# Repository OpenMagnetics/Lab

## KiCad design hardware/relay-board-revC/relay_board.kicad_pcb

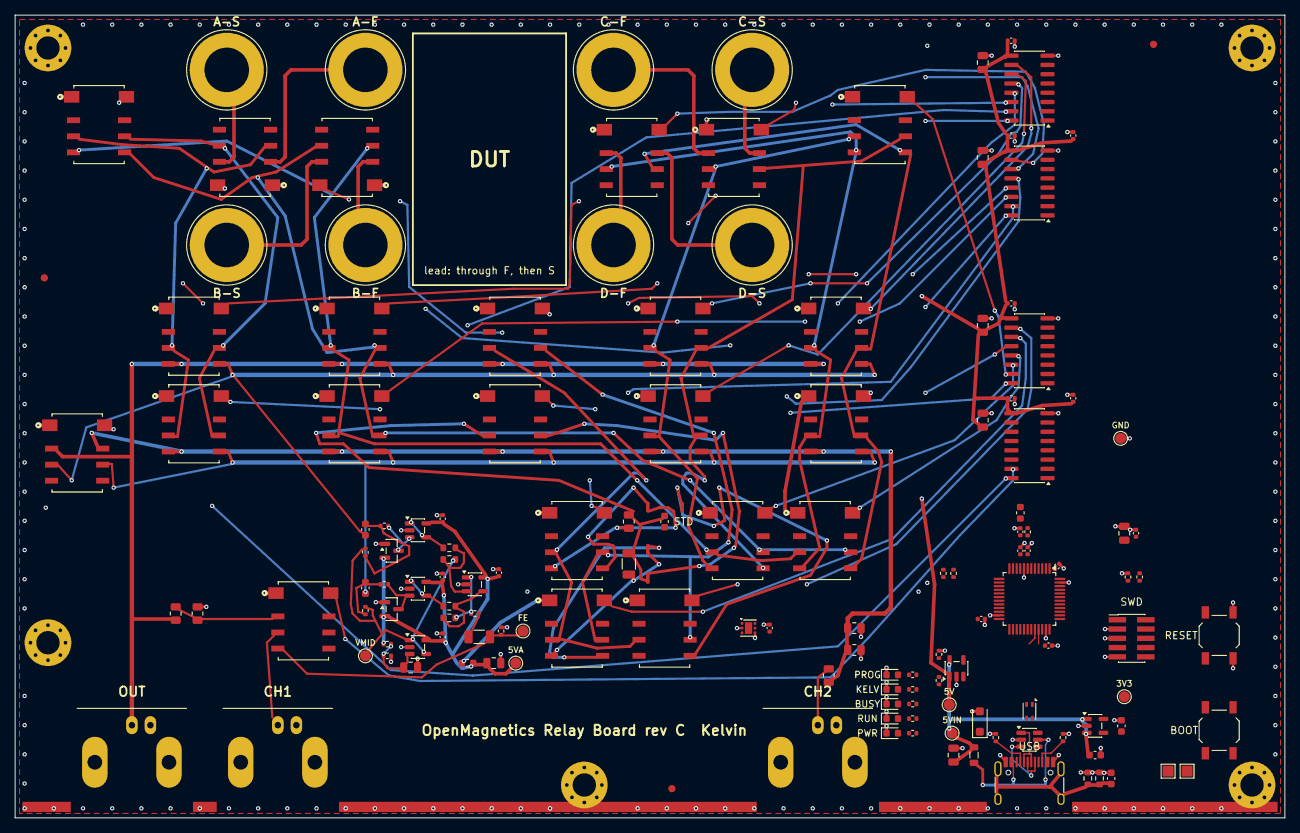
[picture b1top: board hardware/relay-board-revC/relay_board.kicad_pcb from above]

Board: 4 copper layers, 174.0 x 110.0 mm, 157 parts (0 on the bottom side), 126 nets.

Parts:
BOND1, BOND2, BOND3, BOND4, BOND5: GND bonding strip; GND_BondingStrip
C1, C2, C23, C29, C32, C33, C34, C35: C_0805_2012Metric
C3, C4, C20, C21, C30, C31: C_0603_1608Metric
C5, C6, C7, C8, C9, C10, C11, C12, C15, C16, C17, C18, C19, C25, C26, C27, C28, C36: C_0402_1005Metric
C22: C_1206_3216Metric
D1, D5, D6, D7, D8: LED_0603_1608Metric
D2: SOT-23-6
D3, D4: SOT-23
D9: D_SOD-123F
FB1: L_0805_2012Metric
FB2, FB3: L_0603_1608Metric
FID1, FID2, FID3: Fiducial_1mm_Mask2mm
H1, H2, H3, H4, H5: MountingHole_3.2mm_M3_Pad_Via
J1: USB_C_Receptacle_HRO_TYPE-C-31-M-12
J6, J7, J9: BNC_Amphenol_B6252HB-NPP3G-50_Horizontal
J8: PinHeader_2x05_P1.27mm_Vertical_SMD
J10, J11, J12, J13, J14, J15, J16, J17: Banana_Jack_1Pin
K1, K2, K3, K4, K5, K6, K7, K8, K9, K10, K11, K12, K13, K14, K15, K16, K17, K18, K19, K20, K21, K22, K23: G6K-2F-RF-S; Relay_Omron_G6K-2F-RF-S
L1: L_CommonModeChoke_Coilank_ACM2012
NT1, NT2, NT4, NT5: NetTie-2_SMD_Pad0.5mm
R1, R2, R3, R4, R10, R17, R20, R21, R22, R23, R28, R29, R30, R31, R32, R33, R34, R35, R38, R39, R40, R41: R_0402_1005Metric
R5, R12, R13, R14, R15, R16: R_0805_2012Metric
R18: R_1206_3216Metric
R24, R25, R26, R27, R36, R37: R_0603_1608Metric
SW1, SW2: SW_SPST_TL3342
TP1, TP2: TestPoint_Pad_1.5x1.5mm
TP3, TP4, TP5, TP6, TP7, TP8, TP9: TestPoint_Pad_D1.5mm
U1: LQFP-48_7x7mm_P0.5mm
U2, U3, U4, U6: SOIC-16_3.9x9.9mm_P1.27mm
U5, U7, U8, U9, U10, U11: SOT-23-5
U12: WSON-6-1EP_2x2mm_P0.65mm_EP1x1.6mm

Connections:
/+3V3: C2.1, C4.1, C8.1, C9.1, C16.1, C17.1, C36.1, FB3.1, J8.1, R3.1, R32.1, R38.2, R39.2, R41.2, SW1.1, TP2.1, TP5.1, U1.1, U1.24, U1.36, U1.48, U5.5, U12.5
/+3V3A: C18.1, C19.1, FB3.2, U1.9
/+5V: C5.1, C6.1, C7.1, C10.1, C11.1, C12.1, C32.1, C33.1, C34.1, C35.1, FB2.1, K1.1, K2.1, K3.1, K4.1, K5.1, K6.1, K7.1, K8.1, K9.1, K10.1, K11.1, K12.1, K13.1, K14.1, K15.1, K16.1, K17.1, K18.1, K19.1, K20.1, K21.1, K22.1, K23.1, TP3.1, U2.9, U3.9, U4.9, U6.9, U11.1
/+5VA: C25.1, C26.1, C27.1, C28.1, C29.1, D3.2, D4.2, FB2.2, R30.1, TP6.1, U7.5, U8.5, U9.5, U10.5
/+5V_IN: C1.1, C3.1, FB1.2, TP4.1, U5.1, U5.3, U11.5
/BOOT0: R4.1, R17.2, TP1.1, U1.44
/BOOT_SW: R17.1, SW1.2
/BUSY_A: D6.2, R33.2
/CAL_E: K9.3, K19.3, K20.3, K21.3
/CAL_ES: K9.6, K19.6, K20.6, K21.6
/CAL_F: C30.2, K10.3, NT2.1, R5.2, R18.2
/CAL_FS: K10.6, NT2.2
/CC1: J1.A5, R1.1
/CC2: J1.B5, R2.1
/CH1_BNC: J7.1, K23.3
/CH1_NODE: K23.2, R12.2, R13.1
/CH2_NODE: J9.1, R16.2
/COIL_EN: R40.1, U1.25, U11.4
/COIL_FLT: R41.1, U1.26, U11.3
/DUTS_A: J11.1, K11.7
/DUTS_B: J13.1, K12.7
/DUTS_C: J15.1, K13.7
/DUTS_D: J17.1, K14.7
/DUT_A: J10.1, K11.2
/DUT_B: J12.1, K12.2
/DUT_C: J14.1, K13.2
/DUT_D: J16.1, K14.2
/FE_AMP: R25.2, R28.1, U9.1
/FE_BN: R24.1, U8.1, U8.4
/FE_BP: R26.1, U7.1, U7.4
/FE_DM: R24.2, R25.1, U9.4
/FE_DP: R26.2, R27.1, U9.3
/FE_INN: C21.2, R22.1, R23.1
/FE_INP: C20.2, R20.1, R21.1
/FE_N: D4.3, R23.2, U8.3
/FE_OUT: C22.2, K23.4, R29.1, TP8.1
/FE_P: D3.3, R21.2, U7.3
/FE_R: C22.1, R28.2
/GND: BOND1.1, BOND2.1, BOND3.1, BOND4.1, BOND5.1, C1.2, C2.2, C3.2, C4.2, C5.2, C6.2, C7.2, C8.2, C9.2, C10.2, C11.2, C12.2, C15.2, C16.2, C17.2, C18.2, C19.2, C23.2, C25.2, C26.2, C27.2, C28.2, C29.2, C31.2, C32.2, C33.2, C34.2, C35.2, C36.2, D1.1, D2.2, D3.1, D4.1, D5.1, D6.1, D7.1, D8.1, D9.2, H1.1, H2.1, H3.1, H4.1, H5.1, J1.A1, J1.A12, J1.B1, J1.B12, J6.2, J7.2, J8.3, J8.5, J8.9, J9.2, R1.2, R2.2, R4.2, R13.2, R14.2, R15.2, R29.2, R31.2, R36.2, R37.2, R40.2, SW2.2, TP9.1, U1.8, U1.23, U1.35, U1.47, U2.8, U3.8, U4.8, U5.2, U6.8, U7.2, U8.2, U9.2, U10.2, U11.2, U12.2, U12.4
/GPIO1: U1.14, U2.1
/GPIO2: U1.15, U2.2
/GPIO3: U1.16, U2.3
/GPIO4: U1.17, U2.4
/GPIO5: U1.18, U2.5
/GPIO6: U1.19, U2.6
/GPIO7: U1.20, U2.7
/GPIO8: U1.43, U3.1
/GPIO9: U1.42, U3.2
/GPIO10: U1.41, U3.3
/GPIO11: U1.40, U3.4
/GPIO12: U1.39, U3.5
/GPIO13: U1.38, U3.6
/GPIO14: U1.13, U3.7
/GPIO15: U1.10, U4.1
/GPIO16: U1.6, U4.2
/GPIO17: U1.5, U4.3
/GPIO18: U1.4, U4.4
/GPIO19: U1.3, U4.5
/GPIO20: U1.46, U4.6
/GPIO21: U1.45, U4.7
/GPIO22: U1.12, U6.1
/GPIO23: U1.11, U6.2
/I2C_SCL: R38.1, U1.21, U12.1
/I2C_SDA: R39.1, U1.22, U12.6
/K1_COIL: K1.8, U2.16
/K2_COIL: K2.8, U2.15
/K3_COIL: K3.8, U2.14
/K4_COIL: K4.8, U2.13
/K5_COIL: K5.8, U2.12
/K6_COIL: K6.8, U2.11
/K7_COIL: K7.8, U2.10
/K8_COIL: K8.8, U3.16
/K9_COIL: K9.8, U3.15
/K10_COIL: K10.8, U3.14
/K11_COIL: K11.8, U3.13
/K12_COIL: K12.8, U3.12
/K13_COIL: K13.8, U3.11
/K14_COIL: K14.8, U3.10
/K15_COIL: K15.8, U4.16
/K16_COIL: K16.8, U4.15
/K17_COIL: K17.8, U4.14
/K18_COIL: K18.8, U4.13
/K19_COIL: K19.8, U4.12
/K20_COIL: K20.8, U4.11
/K21_COIL: K21.8, U4.10
/K22_COIL: K22.8, U6.16
/K23_COIL: K23.8, U6.15
/KELVIN_A: D7.2, R34.2
/LED_BUSY: R33.1, U1.29
/LED_KELVIN: R34.1, U1.28
/LED_PROG: R35.1, U1.27
/LED_RUN: R10.1, U1.30
/NRST: C15.1, J8.10, R3.2, SW2.1, U1.7
/PROG_A: D8.2, R35.2
/PWR_A: D5.2, R32.2
/RAIL_HI: J6.1, K1.4, K3.4, K5.4, K7.4, K9.4, K22.2, R12.1
/RAIL_LO: K2.4, K4.4, K6.4, K8.4, K10.4, K22.7, R14.1, R15.1, R16.1
/RUN_A: D1.2, R10.2
/SA: K1.6, K2.6, K11.6, K15.6
/SB: K3.6, K4.6, K12.6, K15.5, K17.6, K18.6
/SC: K5.6, K6.6, K13.6, K16.6, K17.5
/SD: K7.6, K8.6, K14.6, K16.5, K18.5
/SNS_HI: C20.1, K1.5, K3.5, K5.5, K7.5, K9.5, K22.3
/SNS_LO: C21.1, K2.5, K4.5, K6.5, K8.5, K10.5, K22.6
/STD1_F: K19.4, NT1.1, R5.1
/STD1_S: K19.5, NT1.2
/STD2_F: K20.4, NT4.1, R18.1
/STD2_S: K20.5, NT4.2
/STD3_F: C30.1, K21.4, NT5.1
/STD3_S: K21.5, NT5.2
/SWCLK: J8.4, U1.37
/SWDIO: J8.2, U1.34
/TA: K1.3, K2.3, K11.3, K15.3
/TB: K3.3, K4.3, K12.3, K15.4, K17.3, K18.3
/TC: K5.3, K6.3, K13.3, K16.3, K17.4
/TD: K7.3, K8.3, K14.3, K16.4, K18.4
/USB_DM: L1.2, U1.32
/USB_DM_CON: D2.1, J1.A7, J1.B7
/USB_DM_ESD: D2.6, L1.3
/USB_DP: L1.1, U1.33
/USB_DP_CON: D2.3, J1.A6, J1.B6
/USB_DP_ESD: D2.4, L1.4
/USB_SHIELD: C31.1, J1.SH, R36.1, R37.1
/VBUS: D2.5, D9.1, FB1.1, J1.A4, J1.A9, J1.B4, J1.B9
/VMID: R20.2, R22.2, R27.2, TP7.1, U10.1, U10.4
/VMID_DIV: C23.1, R30.2, R31.1, U10.3

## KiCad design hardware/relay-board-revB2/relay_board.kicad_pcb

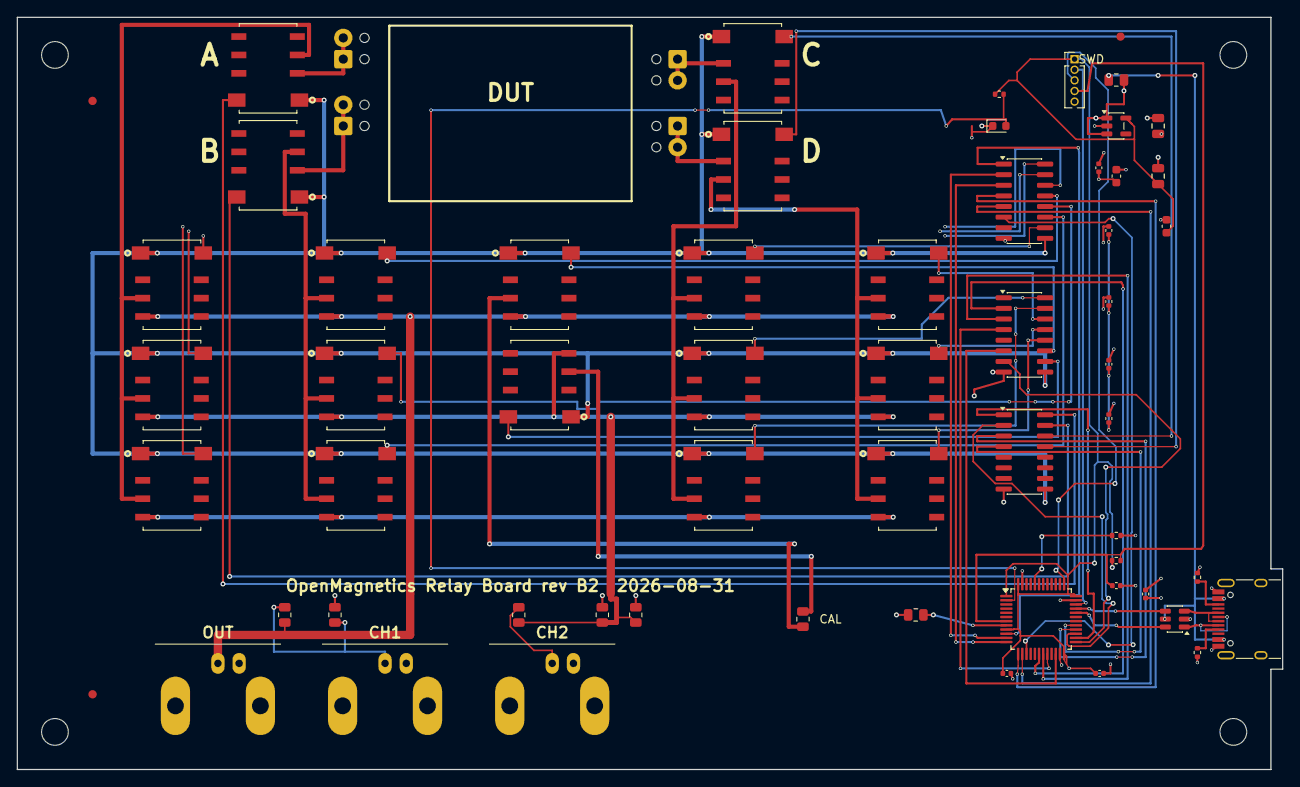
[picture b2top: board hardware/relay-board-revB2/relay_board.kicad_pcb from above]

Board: 4 copper layers, 151.4 x 90.0 mm, 67 parts (0 on the bottom side), 67 nets.

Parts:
C1, C2: C_0805_2012Metric
C3, C4: C_0603_1608Metric
C5, C6, C7, C8, C9, C10, C11, C12, C15: C_0402_1005Metric
D1: LED_0603_1608Metric
D2: SOT-23-6
FID1, FID2, FID3: Fiducial_1mm_Mask2mm
H1, H2, H3, H4: MountingHole_3.2mm_M3
J1: USB_C_Receptacle_HRO_TYPE-C-31-M-12
J2, J3, J4, J5: TerminalBlock_Phoenix_MPT-0,5-2-2.54_1x02_P2.54mm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; TerminalBlock_Phoenix_MPT-0,5-2-2.54_1x02_P2.54mm_Horizontal
J6, J7, J9: BNC_Amphenol_B6252HB-NPP3G-50_Horizontal
J8: PinHeader_1x05_P1.27mm_Vertical
K1, K2, K3, K4, K5, K6, K7, K8, K9, K10, K11, K12, K13, K14, K15, K16, K17, K18: G6K-2F-RF-S; Relay_Omron_G6K-2F-RF-S
R1, R2, R3, R4, R10: R_0402_1005Metric
R5, R9, R11, R12, R13, R14, R15, R16: R_0805_2012Metric
U1: LQFP-48_7x7mm_P0.5mm
U2, U3, U4: SOIC-16_3.9x9.9mm_P1.27mm
U5: SOT-23-5

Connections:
/+3V3: C2.1, C4.1, C8.1, C9.1, J8.1, R3.1, R10.1, U1.1, U1.9, U1.24, U1.36, U1.48, U5.5
/+5V: C1.1, C3.1, C5.1, C6.1, C7.1, C10.1, C11.1, C12.1, K1.1, K2.1, K3.1, K4.1, K5.1, K6.1, K7.1, K8.1, K9.1, K10.1, K11.1, K12.1, K13.1, K14.1, K15.1, K16.1, K17.1, K18.1, R9.2, U2.9, U3.9, U4.9, U5.1, U5.3
/AGND: J6.2, J7.2, J9.2, R11.1, R13.2, R14.2, R15.2
/BOOT0: R4.1, U1.44
/CAL_E: K13.3, R5.1
/CAL_F: K14.3, R5.2
/CC1: J1.A5, R1.1
/CC2: J1.B5, R2.1
/CH1_NODE: J7.1, R12.2, R13.1
/CH2_NODE: J9.1, R16.2
/DUT_A: J2.1, J2.2, K15.2
/DUT_B: J3.1, J3.2, K16.2
/DUT_C: J4.1, J4.2, K17.2
/DUT_D: J5.1, J5.2, K18.2
/GND: C1.2, C2.2, C3.2, C4.2, C5.2, C6.2, C7.2, C8.2, C9.2, C10.2, C11.2, C12.2, C15.2, D1.1, D2.2, J1.A1, J1.A12, J1.B1, J1.B12, J1.S1, J8.5, R1.2, R2.2, R4.2, R11.2, U1.8, U1.23, U1.35, U1.47, U2.8, U3.8, U4.8, U5.2
/GPIO1: U1.10, U2.1
/GPIO2: U1.11, U2.2
/GPIO3: U1.12, U2.3
/GPIO4: U1.13, U2.4
/GPIO5: U1.14, U2.5
/GPIO6: U1.15, U2.6
/GPIO7: U1.16, U2.7
/GPIO8: U1.17, U3.1
/GPIO9: U1.18, U3.2
/GPIO10: U1.19, U3.3
/GPIO11: U1.20, U3.4
/GPIO12: U1.21, U3.5
/GPIO13: U1.22, U3.6
/GPIO14: U1.25, U3.7
/GPIO15: U1.26, U4.1
/GPIO16: U1.27, U4.2
/GPIO17: U1.28, U4.3
/GPIO18: U1.29, U4.4
/K1_COIL: K1.8, U2.16
/K2_COIL: K2.8, U2.15
/K3_COIL: K3.8, U2.14
/K4_COIL: K4.8, U2.13
/K5_COIL: K5.8, U2.12
/K6_COIL: K6.8, U2.11
/K7_COIL: K7.8, U2.10
/K8_COIL: K8.8, U3.16
/K9_COIL: K9.8, U3.15
/K10_COIL: K10.8, U3.14
/K11_COIL: K11.8, U3.13
/K12_COIL: K12.8, U3.12
/K13_COIL: K13.8, U3.11
/K14_COIL: K14.8, U3.10
/K15_COIL: K15.8, U4.16
/K16_COIL: K16.8, U4.15
/K17_COIL: K17.8, U4.14
/K18_COIL: K18.8, U4.13
/LED_A: D1.2, R10.2, U1.2
/NRST: C15.1, J8.4, R3.2, U1.7
/RAIL_HI: J6.1, K1.4, K4.4, K7.4, K10.4, K13.4, R12.1
/RAIL_LINK: K3.4, K6.4, K9.4, K12.4
/RAIL_LO: K2.4, K5.4, K8.4, K11.4, K14.4, R14.1, R15.1, R16.1
/SWCLK: J8.3, U1.37
/SWDIO: J8.2, U1.34
/TA: K1.3, K2.3, K3.3, K15.3
/TB: K4.3, K5.3, K6.3, K16.3
/TC: K7.3, K8.3, K9.3, K17.3
/TD: K10.3, K11.3, K12.3, K18.3
/USB_DM: D2.6, U1.32
/USB_DM_CON: D2.1, J1.A7, J1.B7
/USB_DP: D2.4, U1.33
/USB_DP_CON: D2.3, J1.A6, J1.B6
/VBUS: D2.5, J1.A4, J1.A9, J1.B4, J1.B9, R9.1

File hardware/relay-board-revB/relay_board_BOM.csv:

Comment,Designator,Footprint,Quantity,Manufacturer Part,Description
22uF,"C1,C2",C_0805_2012Metric,2,,C_0805_2012Metric
1uF,"C3,C4",C_0603_1608Metric,2,,C_0603_1608Metric
100nF,"C5,C6,C7,C8,C9,C10,C11,C12,C15",C_0402_1005Metric,9,,C_0402_1005Metric
PWR,D1,LED_0603_1608Metric,1,,LED_0603_1608Metric
USBLC6-2SC6,D2,SOT-23-6,1,ST USBLC6-2SC6,"USB 2.0 ESD array, IEC 61000-4-2 level 4"
USB-C,J1,USB_C_Receptacle_HRO_TYPE-C-31-M-12,1,HRO TYPE-C-31-M-12,"USB-C receptacle, USB 2.0, 16 pin"
DUT A,J2,"TerminalBlock_Phoenix_MPT-0,5-2-2.54_1x02_P2.54mm_Horizontal",1,"Phoenix 1725656 (MPT 0,5/2-2,54)","spring-cage DUT clamp, 2 positions, wire entry from top edge"
DUT B,J3,"TerminalBlock_Phoenix_MPT-0,5-2-2.54_1x02_P2.54mm_Horizontal",1,"Phoenix 1725656 (MPT 0,5/2-2,54)","spring-cage DUT clamp, 2 positions, wire entry from top edge"
DUT C,J4,"TerminalBlock_Phoenix_MPT-0,5-2-2.54_1x02_P2.54mm_Horizontal",1,"Phoenix 1725656 (MPT 0,5/2-2,54)","spring-cage DUT clamp, 2 positions, wire entry from top edge"
DUT D,J5,"TerminalBlock_Phoenix_MPT-0,5-2-2.54_1x02_P2.54mm_Horizontal",1,"Phoenix 1725656 (MPT 0,5/2-2,54)","spring-cage DUT clamp, 2 positions, wire entry from top edge"
BNC SOURCE,J6,BNC_Amphenol_B6252HB-NPP3G-50_Horizontal,1,Amphenol B6252HB-NPP3G-50,50R right-angle BNC jack
BNC CH1,J7,BNC_Amphenol_B6252HB-NPP3G-50_Horizontal,1,Amphenol B6252HB-NPP3G-50,50R right-angle BNC jack
SWD,J8,PinHeader_1x05_P1.27mm_Vertical,1,CNC Tech 3220-05-0100-00,1.27 mm SWD header
BNC CH2,J9,BNC_Amphenol_B6252HB-NPP3G-50_Horizontal,1,Amphenol B6252HB-NPP3G-50,50R right-angle BNC jack
G6K-2F-RF-S DC5,"K1,K2,K3,K4,K5,K6,K7,K8,K9,K10,K11,K12,K13,K14,K15,K16,K17,K18",Relay_Omron_G6K-2F-RF-S,18,Omron G6K-2F-RF-S DC5,"high-frequency DPDT relay, 5 V coil"
5.1k,"R1,R2",R_0402_1005Metric,2,,R_0402_1005Metric
1k,R10,R_0402_1005Metric,1,,R_0402_1005Metric
1k 0.1%,R12,R_0805_2012Metric,1,Vishay TNPW08051K00BEEA,bridge RV1: 1k 0.1% 25 ppm thin film
47R 0.1%,"R13,R16",R_0805_2012Metric,2,Vishay TNPW080547R0BEEA,bridge RV2/RC2: 47R 0.1% 25 ppm thin film
4R7,"R14,R15",R_0805_2012Metric,2,Vishay TNPW08054R70BEEA,bridge RC1 shunt half: 4R7 0.1% (two in parallel = 2R35)
10k,"R3,R4",R_0402_1005Metric,2,,R_0402_1005Metric
100R 0.1%,R5,R_0805_2012Metric,1,Vishay TNPW0805100RBEEA,LOAD standard: 100R 0.1% 25 ppm thin film
0R,"R9,R11",R_0805_2012Metric,2,,R_0805_2012Metric
STM32F072CBT6,U1,LQFP-48_7x7mm_P0.5mm,1,ST STM32F072CBT6,"Cortex-M0, 128K flash, crystal-less USB (HSI48 + CRS)"
TBD62003APG,"U2,U3,U4",SOIC-16_3.9x9.9mm_P1.27mm,3,Toshiba TBD62003AFG,7ch DMOS sink driver (SOIC-16 = AFG suffix)
AP2112K-3.3,U5,SOT-23-5,1,Diodes AP2112K-3.3TRG1,"3.3 V 600 mA LDO, 250 mV dropout"

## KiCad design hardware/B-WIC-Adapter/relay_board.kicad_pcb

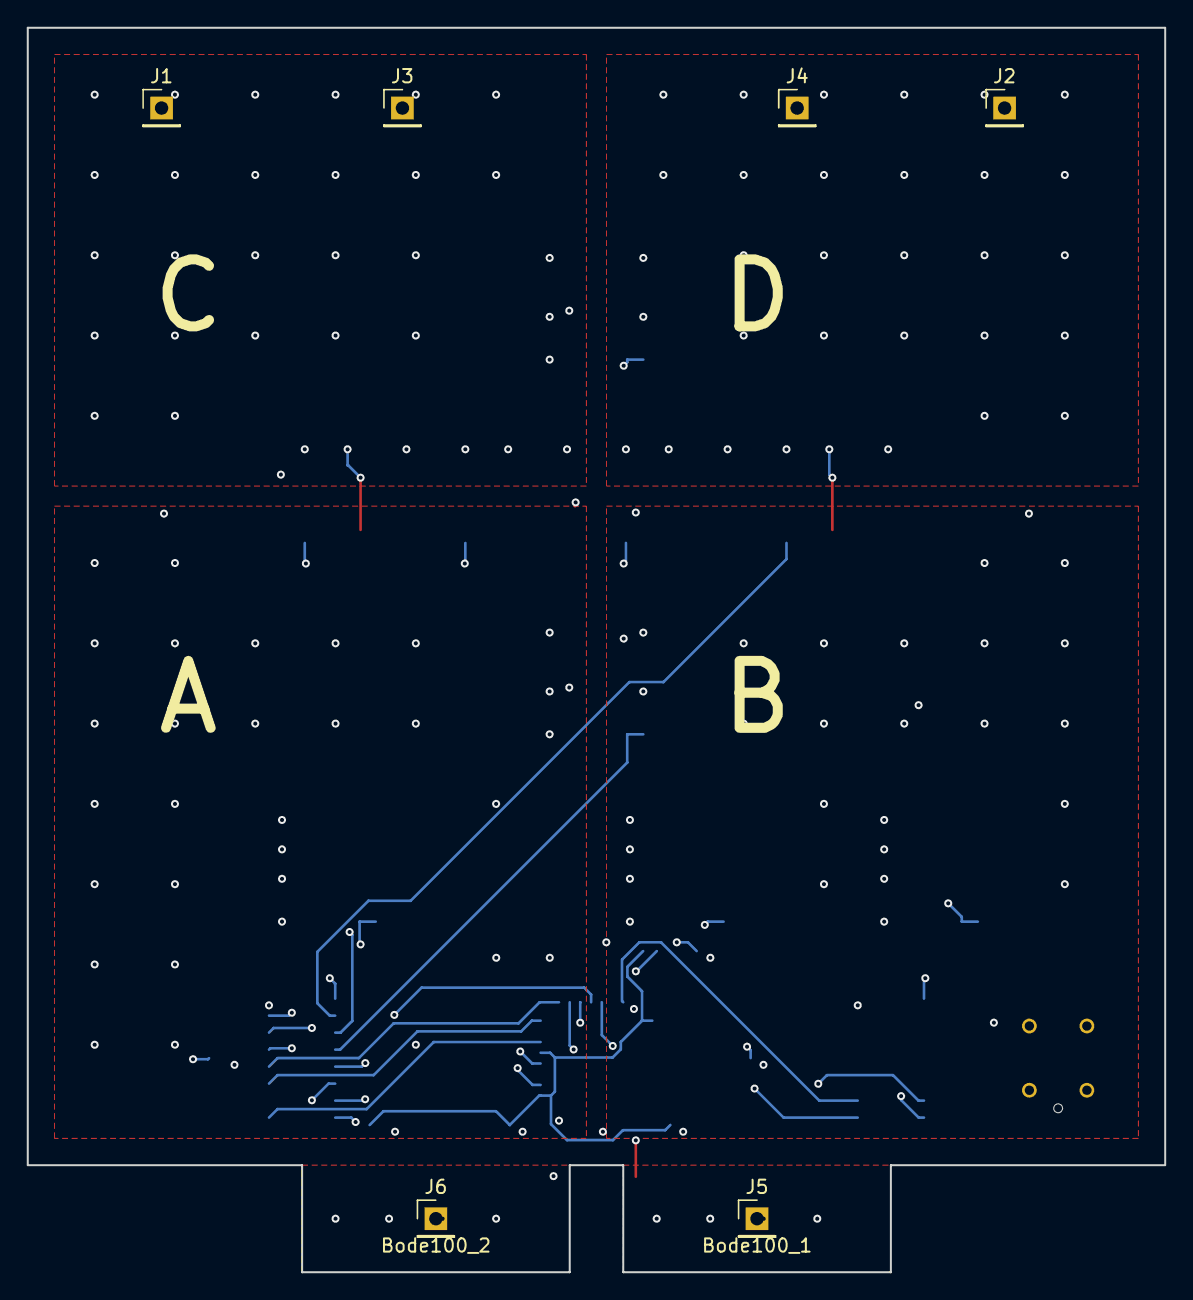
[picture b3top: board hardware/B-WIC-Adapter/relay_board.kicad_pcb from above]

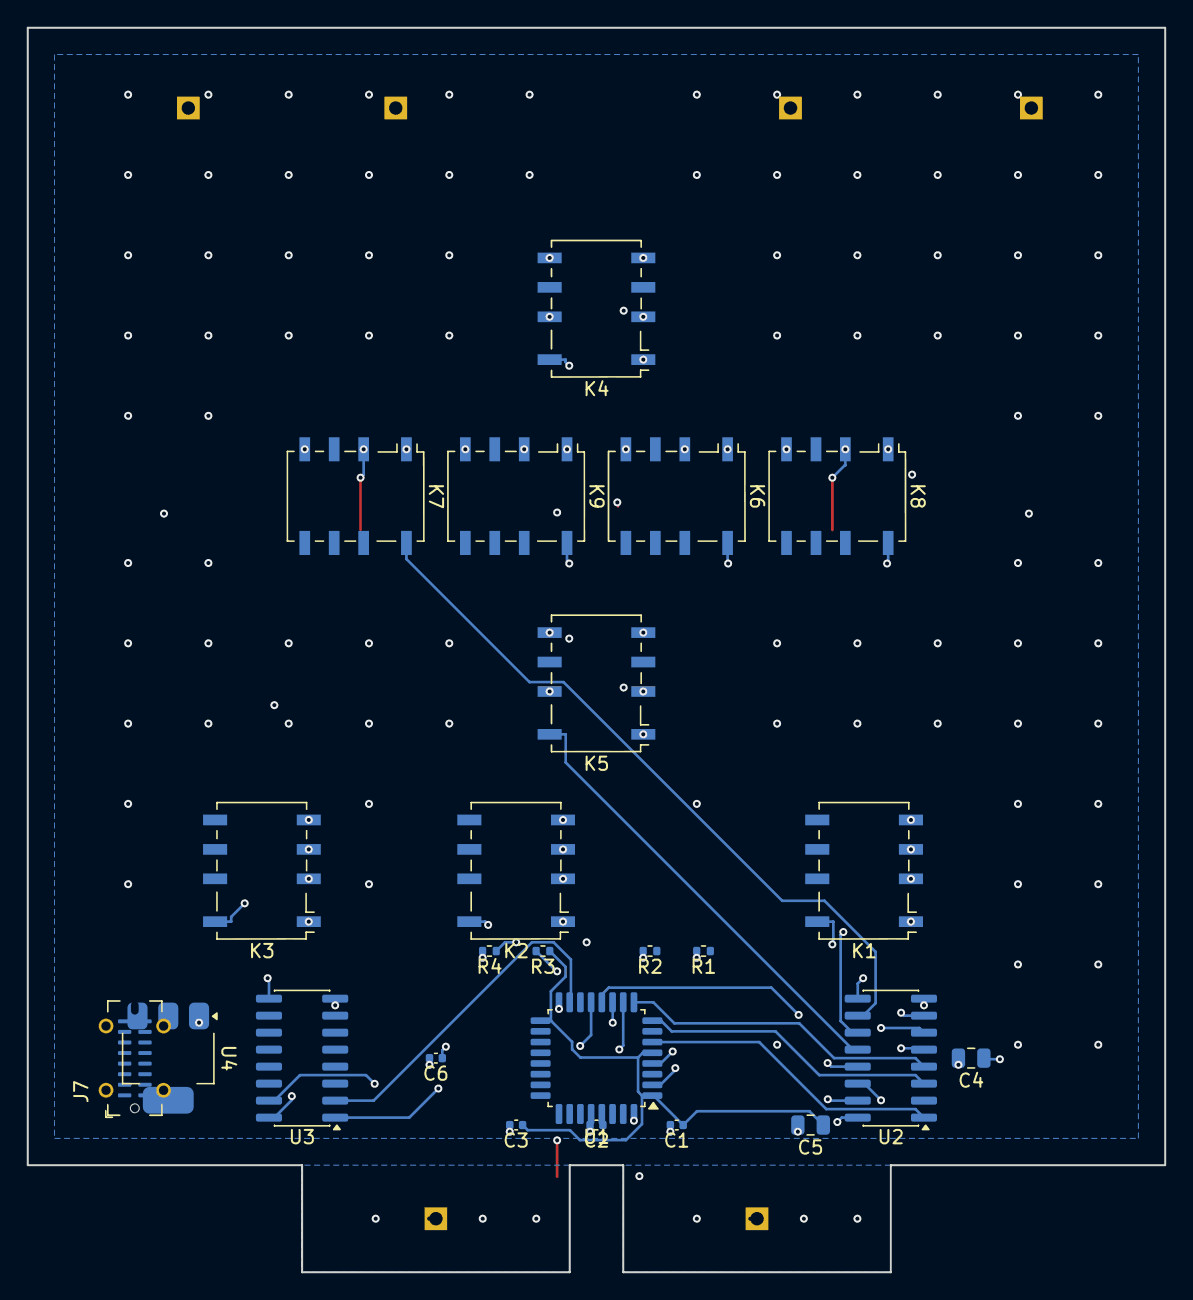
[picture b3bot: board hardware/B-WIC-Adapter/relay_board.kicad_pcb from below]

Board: 4 copper layers, 85.0 x 93.0 mm, 30 parts (24 on the bottom side), 30 nets.

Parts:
C1, C2, C3: 100nF; C_0402_1005Metric
C4, C5: 10uF; C_0805_2012Metric
C6: 1uF; C_0402_1005Metric
J1: A; PinHeader_1x01_P2.54mm_Vertical
J2: B; PinHeader_1x01_P2.54mm_Vertical
J3: C; PinHeader_1x01_P2.54mm_Vertical
J4: D; PinHeader_1x01_P2.54mm_Vertical
J5: Bode100_1; PinHeader_1x01_P2.54mm_Vertical
J6: Bode100_2; PinHeader_1x01_P2.54mm_Vertical
J7: USB-C; USB_C_Receptacle_G-Switch_GT-USB-7051x
K1, K2, K3, K4, K5, K6, K7, K8, K9: G6K-2F-RF-S; Relay_DPDT_Omron_G6K-2F-Y
R1, R2: 5.1k; R_0402_1005Metric
R3, R4: 10k; R_0402_1005Metric
U1: STM32F042K6Tx; LQFP-32_7x7mm_P0.8mm
U2, U3: ULN2003A; SOIC-16_3.9x9.9mm_P1.27mm
U4: AMS1117-3.3; SOT-223-3_TabPin2

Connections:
+3V3: C1.1, C2.1, C3.1, C5.1, R3.1, U1.1, U1.5, U1.17, U4.2
+5V: C4.1, C6.1, K1.1, K2.1, K3.1, K4.1, K5.1, K6.1, K7.1, K8.1, K9.1, U2.9, U3.9, U4.3
A: J1.1, K1.3, K5.2, K5.7, K8.2, K9.2
B: J2.1, K2.3, K5.4, K5.5, K6.2, K7.2
BOOT0: R4.1, U1.2
Bode100_1: J5.1, K1.2
Bode100_2: J6.1, K2.2
C: J3.1, K1.4, K3.4, K4.2, K4.7, K6.4, K8.4
D: J4.1, K3.3, K4.4, K4.5, K7.4, K9.4
GND: C1.2, C2.2, C3.2, C4.2, C5.2, C6.2, R1.2, R2.2, R4.2, U1.16, U1.32, U2.8, U3.3, U3.4, U3.5, U3.6, U3.7, U3.8, U4.1
GPIO0: U1.6, U2.1
GPIO1: U1.7, U2.2
GPIO2: U1.8, U2.3
GPIO3: U1.9, U2.4
GPIO4: U1.10, U2.5
GPIO5: U1.11, U2.6
GPIO6: U1.12, U2.7
GPIO7: U1.13, U3.1
GPIO8: U1.15, U3.2
K1_COIL: K1.8, U2.16
K2_COIL: K2.8, U2.15
K3_COIL: K3.8, U2.14
K4_COIL: K4.8, U2.13
K5_COIL: K5.8, U2.12
K6_COIL: K6.8, U2.11
K7_COIL: K7.8, U2.10
K8_COIL: K8.8, U3.16
K9_COIL: K9.8, U3.15
NRST: R3.2, U1.4
R3_COM: K2.4, K3.2

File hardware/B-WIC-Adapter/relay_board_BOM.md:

# OpenMagnetics Automated Relay Board - Bill of Materials
# Generated by generate_board.py

| Ref | Qty | Value | Description | Package | Part Number |
|-----|-----|-------|-------------|---------|-------------|
| U1 | 1 | STM32F042K6T6 | ARM Cortex-M0 MCU, crystal-less USB | LQFP-32 | STM32F042K6T6 |
| U2 | 1 | ULN2003A | 7-ch Darlington driver (K1-K7) | SOIC-16 | ULN2003ADR |
| U3 | 1 | ULN2003A | 7-ch Darlington driver (K8-K9) | SOIC-16 | ULN2003ADR |
| U4 | 1 | AMS1117-3.3 | 3.3V LDO regulator | SOT-223 | AMS1117-3.3 |
| K1-K9 | 9 | G6K-2F-RF-S DC4.5 | DPDT RF signal relay | SMD | G6K-2F-RF-S DC4.5 |
| J1 | 1 | USB-C | USB Type-C receptacle | SMD | USB4105-GF-A |
| J2 | 1 | Bode100_2 | Edge connector pad (left) | Custom | - |
| J3 | 1 | Bode100_1 | Edge connector pad (right) | Custom | - |
| J4 | 1 | WAGO 2060 | Spring terminal - DUT A | SMD | 2060-451/998-404 |
| J5 | 1 | WAGO 2060 | Spring terminal - DUT B | SMD | 2060-451/998-404 |
| J6 | 1 | WAGO 2060 | Spring terminal - DUT C | SMD | 2060-451/998-404 |
| J7 | 1 | WAGO 2060 | Spring terminal - DUT D | SMD | 2060-451/998-404 |
| C1-C3 | 3 | 100nF | Decoupling, STM32 | 0402 | - |
| C4,C5 | 2 | 100nF | Decoupling, ULN2003A | 0402 | - |
| C6-C14 | 9 | 100nF | Decoupling, relay coils | 0402 | - |
| C15 | 1 | 10uF | Bulk, 5V rail | 0805 | - |
| C16 | 1 | 10uF | Bulk, 3.3V rail | 0805 | - |
| C17 | 1 | 1uF | USB VBUS filter | 0402 | - |
| R1,R2 | 2 | 5.1k | USB-C CC pull-down | 0402 | - |
| R3 | 1 | 10k | NRST pull-up | 0402 | - |
| R4 | 1 | 10k | BOOT0 pull-down | 0402 | - |

## Total unique parts: 11
## Total component count: ~40

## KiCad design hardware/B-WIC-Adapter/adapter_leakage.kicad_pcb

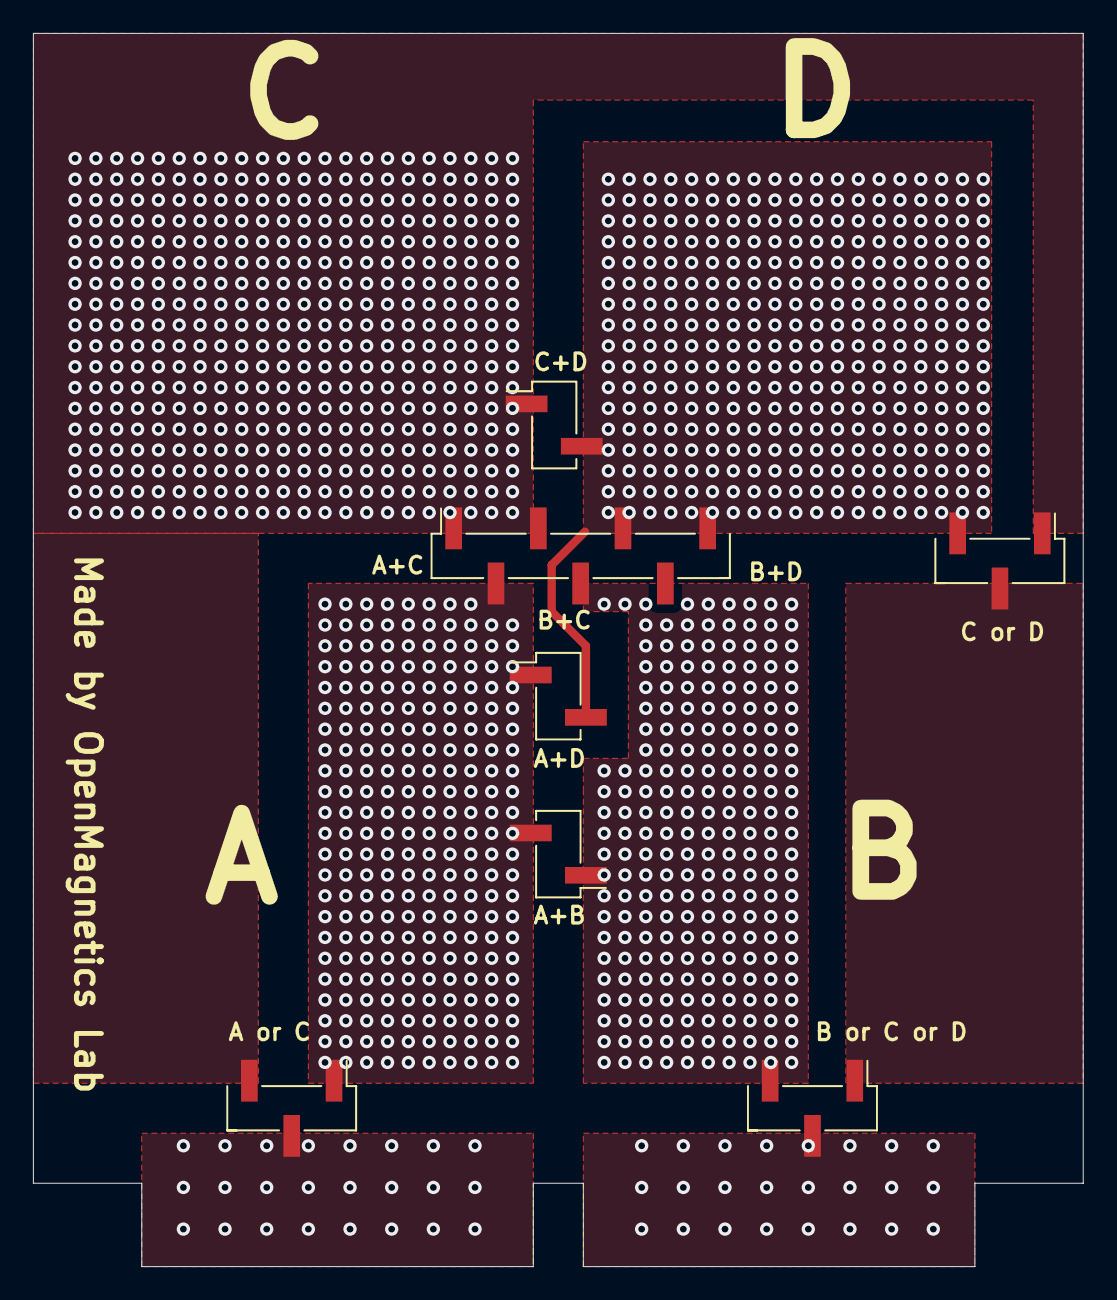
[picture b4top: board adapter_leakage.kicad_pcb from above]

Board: 2 copper layers, 63.0 x 74.0 mm, 7 parts (0 on the bottom side), 5 nets.

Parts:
CC_Bottom1: Conn_01x02; PinHeader_1x02_P2.54mm_Vertical_SMD_Pin1Left
CC_Top1: Conn_01x02; PinHeader_1x02_P2.54mm_Vertical_SMD_Pin1Left
Cum_Dif1: Conn_01x07_MountingPin; PinHeader_1x07_P2.54mm_Vertical_SMD_Pin1Right
J1: Conn_01x02; PinHeader_1x02_P2.54mm_Vertical_SMD_Pin1Left
Pri_Sec_Left1: Conn_01x03; PinHeader_1x03_P2.54mm_Vertical_SMD_Pin1Left
Pri_Sec_Right1: Conn_01x03; PinHeader_1x03_P2.54mm_Vertical_SMD_Pin1Left
Secondary_multiplex1: Conn_01x03; PinHeader_1x03_P2.54mm_Vertical_SMD_Pin1Left

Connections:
/A: CC_Bottom1.2, Cum_Dif1.2, J1.1, Pri_Sec_Left1.1
/B: CC_Bottom1.1, Cum_Dif1.4, Pri_Sec_Right1.3
/C: CC_Top1.1, Cum_Dif1.1, Cum_Dif1.3, Pri_Sec_Left1.3, Secondary_multiplex1.1
/CorD: Pri_Sec_Right1.1, Secondary_multiplex1.2
/D: CC_Top1.2, Cum_Dif1.5, Cum_Dif1.7, J1.2, Secondary_multiplex1.3

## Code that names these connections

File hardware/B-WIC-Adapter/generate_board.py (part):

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        c.move(cap_x + i * 12, 200)

    # --- DUT connectors ---
    for i, (ref, label) in enumerate([('J1', 'DUT_A'), ('J2', 'DUT_B'), ('J3', 'DUT_C'), ('J4', 'DUT_D')]):
        j = sch.components.add('Connector_Generic:Conn_01x01', ref, label)
        j.footprint = 'Connector_PinHeader_2.54mm:PinHeader_1x01_P2.54mm_Vertical'
        j.move(220 + i * 20, 320)
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
    # --- MCU GPIO connections ---
    gpio_map = {
        '6': 'GPIO0',   # PA0
        '7': 'GPIO1',   # PA1
        '8': 'GPIO2',   # PA2
        '9': 'GPIO3',   # PA3
        '10': 'GPIO4',  # PA4
        '11': 'GPIO5',  # PA5
        '12': 'GPIO6',  # PA6
        '13': 'GPIO7',  # PA7
        '15': 'GPIO8',  # PB1
    }
    for pin_num, gpio_name in gpio_map.items():
        sch.add_label(gpio_name, pin=('U1', pin_num))

    # MCU USB pins
    sch.add_label('USB_DM', pin=('U1', '21'))  # PA11
    sch.add_label('USB_DP', pin=('U1', '22'))  # PA12

    # MCU debug pins
    sch.add_label('SWDIO', pin=('U1', '23'))   # PA13
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    for pin_num in unused_mcu:
        sch.add_label(f'NC_U1_{pin_num}', pin=('U1', pin_num))

    # --- ULN2003A #1 connections (GPIO0-6 -> K1-K7) ---
    for i in range(7):
        sch.add_label(f'GPIO{i}', pin=('U2', str(i + 1)))       # Input
        sch.add_label(f'K{i+1}_COIL', pin=('U2', str(16 - i)))  # Output
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    sch.add_label('GND', pin=('U2', '8'))
    sch.add_label('+5V', pin=('U2', '9'))

    # --- ULN2003A #2 connections (GPIO7-8 -> K8-K9) ---
    sch.add_label('GPIO7', pin=('U3', '1'))
    sch.add_label('GPIO8', pin=('U3', '2'))
    sch.add_label('K8_COIL', pin=('U3', '16'))
    sch.add_label('K9_COIL', pin=('U3', '15'))
    sch.add_label('GND', pin=('U3', '8'))
    sch.add_label('+5V', pin=('U3', '9'))

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    sch.add_label('D', pin=('J4', '1'))

    # --- Bode100 connections ---
    sch.add_label('Bode100_1', pin=('J5', '1'))
    sch.add_label('Bode100_2', pin=('J6', '1'))

    # --- Voltage regulator ---
    sch.add_label('VBUS', pin=('U4', '3'))    # Vin
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
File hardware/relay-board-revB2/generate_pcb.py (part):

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            net_name = f"/RAIL_{rail}"
            self.via(x, RAIL_Y[rail], net_name)
            self.track([(x, RAIL_Y[rail]), (x, 109.0)], net_name, width=1.0)
        # HI runs to the SOURCE BNC pin; LO wraps around R14's AGND pad
        # into the RC1 shunt pad from the east.
        source = self.pad_position("J6", 1)
        self.track([(DESCENT_HI_X, 109.0), (DESCENT_HI_X, 113.9),
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                    d2_dp_con], "/USB_DP_CON", width=PLAIN_TRACK)
        self.track([dm_b, (181.0, dm_b[1]), (180.3, d2_dm_con[1]),
                    d2_dm_con], "/USB_DM_CON", width=PLAIN_TRACK)
        # MCU-side pair, hopping to B.Cu across the GPIO14 / NRST F.Cu
        # verticals (x 167.1-167.9), back to F.Cu for the pad entries.
        d2_dp = self.pad_position("D2", 4)       # (177.36, 111.05)
        d2_dm = self.pad_position("D2", 6)       # (177.36, 112.95)
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        self.track([d2_dp, (168.9, d2_dp[1])], "/USB_DP", width=PLAIN_TRACK)
        self.via(168.9, d2_dp[1], "/USB_DP", size=0.4, drill=0.25)
        self.track([(168.9, d2_dp[1]), (166.35, d2_dp[1]),
                    (165.75, pa12[1])], "/USB_DP",
                   layer=pcbnew.B_Cu, width=PLAIN_TRACK)
        self.via(165.75, pa12[1], "/USB_DP", size=0.4, drill=0.25)
        self.track([(165.75, pa12[1]), pa12], "/USB_DP", width=PLAIN_TRACK)
        self.track([d2_dm, (169.3, d2_dm[1]), (169.0, 112.75)], "/USB_DM",
                   width=PLAIN_TRACK)
        self.via(169.0, 112.75, "/USB_DM", size=0.4, drill=0.25)
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            x, y = pad[0] + dx, pad[1] + dy
            self.track([pad, (x, y)], "/GND", width=PLAIN_TRACK)
            self.via(x, y, "/GND", size=0.4, drill=0.25)
        # pin 23: small via clear of pads 22/24 and the GPIO13 entry
        pad23 = self.pad_position("U1", "23")
        self.track([(pad23[0], 116.9), (162.45, 117.5)], "/GND",
                   width=0.15)
        self.via(162.45, 117.5, "/GND", size=0.4, drill=0.25)
        # U3 ground pad: the coil corridors and the GPIO14 In1 transplant
        # box out the safety fanout -- stub south to a via in the gap
        # between the +5V return (y=80.2) and the K5 corridor (y=86.0)
        u3_8 = self.pad_position("U3", 8)
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            if cap == "C11":
                gnd_via_y = ground[1] + 1.93   # south side, under pad 1
            elif cap == "C6":
                gnd_via_y = ground[1] + 1.38   # south side: GPIO8 band above
            else:
                gnd_via_y = ground[1] - 1.32
            if cap in ("C6", "C11"):
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        self.track([c8_gnd, (156.6, 119.15)], "/GND", width=PLAIN_TRACK)
        self.via(156.6, 119.15, "/GND", size=0.4, drill=0.25)

        # GPIO2/3/9/10/13 and NRST: freerouting fails a different subset
        # of these every round -- the MCU approach corridors are saturated.
        # Deterministic lanes, planar by construction: F.Cu entries never
        # conflict with B.Cu lanes.

        # GPIO9/10: west stub off U3 (pads are 1.95 long -- stay west of
        # x 154.55 edge), up into the U2/U3 gap band at y 71.1/71.6 (clear
        # of the K4/K13 coil via rings), east on F.Cu, B.Cu downcomers at
        # 169.6/170.1, west along B.Cu lanes 118.5/119.15, F entries.
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            u1_pad = self.pad_position("U1", u1_pin)
            net_name = self.board.FindFootprintByReference("U3")                            .FindPadByNumber(str(u3_pin)).GetNetname()
            if u1_pin == 18:
                # via jogged south-east so the GPIO1 downcomer clears it
                self.track([u3_pad, (west_x, u3_pad[1]), (west_x, gap_y),
                            (169.6, gap_y), (169.8, 72.1), (169.8, 72.5)],
                           net_name, width=PLAIN_TRACK)
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                self.track([(u1_pad[0], lane_y), u1_pad], net_name,
                           width=PLAIN_TRACK)

        # GPIO13 -> U1.22, all F.Cu: down the west strip at x 153.55
        # (R11 moved west to free this), east along y 119.7 between the
        # C8 pads and the CC1 lane, straight up into pad 22.
        u3_6 = self.pad_position("U3", 6)
        pad22 = self.pad_position("U1", 22)
        self.track([u3_6, (153.55, u3_6[1]), (153.55, 119.7),
                    (pad22[0], 119.7), pad22], "/GPIO13",
                   width=PLAIN_TRACK)

        # GPIO2/3 -> U1.11/12 (west row): west stubs off U2, down F.Cu at
        # x 151.3/151.9 (east of the crossbar rails, west of the MCU strip
        # parts), B.Cu hops under the GPIO13 descent, west-row entries.
        u2_2 = self.pad_position("U2", 2)
        pad11 = self.pad_position("U1", 11)
        self.track([u2_2, (151.7, u2_2[1]), (151.7, 113.95)], "/GPIO2",
                   width=PLAIN_TRACK)
        self.via(151.7, 113.95, "/GPIO2", size=0.4, drill=0.25)
        self.track([(151.7, 113.95), (154.6, 113.95)], "/GPIO2",
                   layer=pcbnew.B_Cu, width=PLAIN_TRACK)
        self.via(154.6, 113.95, "/GPIO2", size=0.4, drill=0.25)
        self.track([(154.6, 113.95), (154.9, 114.25), pad11], "/GPIO2",
                   width=PLAIN_TRACK)
        u2_3 = self.pad_position("U2", 3)
        pad12 = self.pad_position("U1", 12)
        self.track([u2_3, (152.3, u2_3[1]), (152.3, 114.75)], "/GPIO3",
                   width=PLAIN_TRACK)
        self.via(152.3, 114.75, "/GPIO3", size=0.4, drill=0.25)
        self.track([(152.3, 114.75), (154.35, 114.75)], "/GPIO3",
                   layer=pcbnew.B_Cu, width=PLAIN_TRACK)
        self.via(154.35, 114.75, "/GPIO3", size=0.4, drill=0.25)
        self.track([(154.35, 114.75), pad12], "/GPIO3", width=PLAIN_TRACK)

        # GPIO1 -> U1.10 (west row): out over the top of U2, east
        # downcomer, B.Cu lane at 114.95 under the pad row, entry into
        # pad 10 from the east under the body.
        u2_1 = self.pad_position("U2", 1)
        pad10 = self.pad_position("U1", 10)
        self.track([u2_1, (154.9, u2_1[1]), (154.9, 55.6), (164.45, 55.6)],
                   "/GPIO1", width=PLAIN_TRACK)
        self.via(164.45, 55.6, "/GPIO1", size=0.4, drill=0.25)
        self.track([(164.45, 55.6), (164.55, 56.2), (164.55, 109.15),
                    (157.45, 109.15),
                    (157.45, 113.55), (157.0, 113.75)],
                   "/GPIO1", layer=pcbnew.B_Cu, width=PLAIN_TRACK)
        self.via(157.0, 113.75, "/GPIO1", size=0.4, drill=0.25)
        self.track([(157.0, 113.75), (156.4, 113.75)], "/GPIO1",
                   width=0.15)

        # GPIO11 -> U1.20: through the U3 pin-4/5 row gap, west strip at
        # 153.25, jog west of the GPIO13 descent, B.Cu lane at 117.9,
        # south entry between the lane-9 and lane-10 vias.
        u3_4 = self.pad_position("U3", 4)
        pad20 = self.pad_position("U1", 20)
        self.track([u3_4, (152.85, u3_4[1]), (152.85, 117.9)], "/GPIO11",
                   width=PLAIN_TRACK)
        self.via(152.85, 117.9, "/GPIO11", size=0.4, drill=0.25)
        self.track([(152.85, 117.9), (160.95, 117.9)], "/GPIO11",
                   layer=pcbnew.B_Cu, width=PLAIN_TRACK)
        self.via(160.95, 117.9, "/GPIO11", size=0.4, drill=0.25)
        self.track([(160.95, 117.9), (pad20[0], 117.2), pad20], "/GPIO11",
                   width=0.15)

        # SWDIO -> U1.34: B.Cu drop from the J8 through-hole down the
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        self.track([(165.35, 110.05), (164.6, 110.25)], "/SWDIO",
                   width=0.13)

        # GPIO4/5/17/18: far-east descent fan. Ordering rule: the
        # westmost descent carries the shallowest transfer lane, so the
        # eastern descents' transfers pass below their neighbours' ends.
        # F.Cu hops carry each transfer over the GPIO9/10 downcomers and
        # (for GPIO5) over the GPIO17/18 entry verticals.
        u4_4 = self.pad_position("U4", 4)
        pad29 = self.pad_position("U1", 29)
        self.track([u4_4, (154.85, u4_4[1]), (154.85, 92.0),
                    (171.9, 92.0)], "/GPIO18", width=PLAIN_TRACK)
        self.via(171.9, 92.0, "/GPIO18", size=0.4, drill=0.25)
        self.track([(171.9, 92.0), (171.9, 115.9), (171.15, 115.9)],
                   "/GPIO18", layer=pcbnew.B_Cu, width=PLAIN_TRACK)
        self.via(171.15, 115.9, "/GPIO18", size=0.4, drill=0.25)
        self.track([(171.15, 115.9), (169.25, 115.9)], "/GPIO18",
                   width=0.15)
        self.via(169.25, 115.9, "/GPIO18", size=0.4, drill=0.25)
        self.track([(169.25, 115.9), (162.9, 115.9), (162.9, 112.75)],
                   "/GPIO18", layer=pcbnew.B_Cu, width=PLAIN_TRACK)
        self.via(162.9, 112.75, "/GPIO18", size=0.4, drill=0.25)
        self.track([(162.9, 112.75), (163.425, 112.75), pad29], "/GPIO18",
                   width=0.15)

        u4_3 = self.pad_position("U4", 3)
        pad28 = self.pad_position("U1", 28)
        self.track([u4_3, (154.85, u4_3[1]), (154.85, 90.73),
                    (172.5, 90.73)], "/GPIO17", width=PLAIN_TRACK)
        self.via(172.5, 90.73, "/GPIO17", size=0.4, drill=0.25)
        self.track([(172.5, 90.73), (172.5, 116.55), (170.9, 116.55)],
                   "/GPIO17", layer=pcbnew.B_Cu, width=PLAIN_TRACK)
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
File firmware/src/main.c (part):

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/* RUN LED: PA9 on rev C (south row, beside the other status LEDs), PC13 on rev B. */
#ifdef BOARD_REVC
#define RUN_PORT    GPIOA
#define RUN_PIN     GPIO9
#else
#define RUN_PORT    GPIOC
#define RUN_PIN     GPIO13
#endif

void sys_tick_handler(void)
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 * is hardwired). PB12 is the coil-supply enable, PB13 its fault; PB10/PB11
 * are I2C2 (TMP117). Every relay-drive pin faces the drivers (relay_map_revc.h). */
#ifdef BOARD_REVC
#define LED_BUSY   GPIOA, GPIO8
#define LED_KELVIN GPIOB, GPIO15
#define LED_PROG_PORT GPIOB
#define LED_PROG_PIN  GPIO14
#define FIXED_A     (GPIO8 | GPIO9)                      /* BUSY, RUN */
#define FIXED_C     0u
#define FIXED_B     (GPIO10 | GPIO11 | GPIO12 | GPIO13 | GPIO14 | GPIO15)
static void led_set(uint32_t port, uint16_t pin, int on)
{
    if (on) {
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#else
#define FIXED_A     0u
#define FIXED_B     0u
#define FIXED_C     GPIO13
#define led(which, on) ((void)0)
#endif

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     * PA9/PA10, USART2 PA14/PA15, USB PA11/PA12) never touches PB14, so it
     * stays lit for the whole firmware update. */
    rcc_periph_clock_enable(RCC_GPIOB);
    gpio_mode_setup(LED_PROG_PORT, GPIO_MODE_OUTPUT, GPIO_PUPD_NONE, LED_PROG_PIN);
    gpio_set(LED_PROG_PORT, LED_PROG_PIN);
#endif
    rcc_periph_clock_enable(RCC_SYSCFG_COMP);
    SYSCFG_CFGR1 = (SYSCFG_CFGR1 & ~(uint32_t)SYSCFG_CFGR1_MEM_MODE)
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    /* RUN LED (sys_tick_handler) and rev C status LEDs on the south row. */
    gpio_mode_setup(RUN_PORT, GPIO_MODE_OUTPUT, GPIO_PUPD_NONE, RUN_PIN);
#ifdef BOARD_REVC
    gpio_mode_setup(GPIOA, GPIO_MODE_OUTPUT, GPIO_PUPD_NONE, GPIO8);
    gpio_mode_setup(GPIOB, GPIO_MODE_OUTPUT, GPIO_PUPD_NONE, GPIO14 | GPIO15);
    gpio_clear(GPIOA, GPIO8);
    gpio_clear(GPIOB, GPIO14 | GPIO15);
#endif

    /* Every other pin to analog mode: no floating digital inputs (lowest
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    for (unsigned port = 0; port < 4u; port++) {
        uint16_t spare = (uint16_t)(~used[port] & 0xFFFFu);
        if (port == 2u) {
            spare &= GPIO13 | GPIO14 | GPIO15;           /* the F072CB has PC13..15 only */
        } else if (port == 3u) {
            spare &= GPIO0 | GPIO1;                      /* and PF0/PF1 */
        }
        if (spare) {
            gpio_mode_setup(ports[port], GPIO_MODE_ANALOG, GPIO_PUPD_NONE, spare);
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
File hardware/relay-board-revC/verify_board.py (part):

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        (("J8", "4"), "/SWCLK", "Cortex header pin 4 = SWCLK"),
        (("J8", "10"), "/NRST", "Cortex header pin 10 = nRESET"),
        (("J8", "1"), "/+3V3", "Cortex header pin 1 = VTref"),
        (("U1", "33"), "/USB_DP", "PA12 is USB D+"),
        (("U1", "32"), "/USB_DM", "PA11 is USB D-"),
        (("D2", "1"), "/USB_DM_CON", "ESD I/O1 in: connector D-"),
        (("D2", "6"), "/USB_DM_ESD", "ESD I/O1 out"),
        (("D2", "3"), "/USB_DP_CON", "ESD I/O2 in: connector D+"),
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        (("U11", "5"), "/+5V_IN", "coil switch input on +5V_IN"),
        (("U11", "1"), "/+5V", "coil switch output is the coil rail"),
        (("U11", "4"), "/COIL_EN", "coil switch enable from the MCU"),
        (("U1", "25"), "/COIL_EN", "PB12 drives COIL_EN"),
        (("R40", "2"), "/GND", "COIL_EN pulled low: coils off through reset"),
        (("U1", "26"), "/COIL_FLT", "PB13 reads the coil-switch fault flag"),
        (("J1", "SH"), "/USB_SHIELD", "USB shield on its own net (R37 strap / RC option)"),
        (("R37", "2"), "/GND", "R37 bonds the shield to ground"),
        (("U12", "1"), "/I2C_SCL", "TMP117 SCL"),
        (("U12", "6"), "/I2C_SDA", "TMP117 SDA"),
        (("U1", "21"), "/I2C_SCL", "PB10 is I2C2 SCL"),
        (("U1", "22"), "/I2C_SDA", "PB11 is I2C2 SDA"),
        (("R10", "1"), "/LED_RUN", "RUN LED driven from PA9"),
        (("U1", "30"), "/LED_RUN", "PA9 is LED_RUN"),
        (("D1", "2"), "/RUN_A", "RUN LED anode behind its resistor"),
        (("D1", "1"), "/GND", "LED cathode to ground"),
        (("R32", "1"), "/+3V3", "PWR LED hardwired to +3V3"),
        (("U1", "29"), "/LED_BUSY", "PA8 drives BUSY"),
        (("U1", "28"), "/LED_KELVIN", "PB15 drives KELVIN"),
        (("U1", "27"), "/LED_PROG", "PB14 drives PROG"),
        (("D8", "2"), "/PROG_A", "PROG LED anode behind its resistor"),
        (("R1", "1"), "/CC1", "CC1 pulldown present"),
        (("U5", "5"), "/+3V3", "LDO output drives +3V3"),
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    for amp in ("U7", "U8", "U9", "U10"):
        if pin_to_net.get((amp, "5")) != "/+5VA" or pin_to_net.get((amp, "2")) != "/GND":
            fail(f"{amp} supply pins not on +5VA/GND")
    if any(name == "/AGND" for name in pin_to_net.values()):
        fail("an AGND net still exists: rev C uses one unified ground")
    relays = [r for r in components if r.startswith("K")]
    if len(relays) != b2.RELAY_COUNT:
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
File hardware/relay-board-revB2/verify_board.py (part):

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
        # LOAD: isolation + K13 + K14 -> rails joined only THROUGH R5.
        union = union_for(iso | {"K13", "K14"}, config)
        hi_leg = any(union.together("/RAIL_HI", pin_to_net.get(("R5", pin), "?"))
                     for pin in ("1", "2"))
        lo_leg = any(union.together("/RAIL_LO", pin_to_net.get(("R5", pin), "?"))
                     for pin in ("1", "2"))
        direct = union.together("/RAIL_HI", "/RAIL_LO")
        if not (hi_leg and lo_leg and not direct):
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        (("R4", "2"), "/GND", "BOOT0 pulled down -> boots from flash"),
        (("U1", "34"), "/SWDIO", "SWDIO reaches"),
        (("J8", "2"), "/SWDIO", "SWD header carries SWDIO"),
        (("U1", "33"), "/USB_DP", "PA12 is USB D+"),
        # USBLC6 is flow-through: pins 1&6 = I/O1 (one line), 3&4 = I/O2
        (("D2", "1"), "/USB_DM_CON", "I/O1 in: connector D-"),
        (("D2", "6"), "/USB_DM", "I/O1 out: MCU D- (internally tied to pin 1)"),
        (("D2", "3"), "/USB_DP_CON", "I/O2 in: connector D+"),
        (("D2", "4"), "/USB_DP", "I/O2 out: MCU D+ (internally tied to pin 3)"),
        (("J1", "A6"), "/USB_DP_CON", "connector D+ on the protected side"),
        (("J1", "A7"), "/USB_DM_CON", "connector D- on the protected side"),
        # Device:LED / LED_0603 pin 1 = cathode: drive on pin 2 (anode)
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
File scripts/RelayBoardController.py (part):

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}
#: K13/K14: the LOAD-standard column -- one 100R 0.1% between two full-length
#: column buses, reached through the same contact structure as a terminal.
LOAD_HI_BIT = 12             # K13: CAL_E -> RAIL_HI
LOAD_LO_BIT = 13             # K14: CAL_F -> RAIL_LO
#: K15..K18: per-terminal isolation. COM = terminal node, NC = clamp,
#: NO = nothing (the open contact IS the open standard).
ISOLATE_BITS = {"A": 14, "B": 15, "C": 16, "D": 17}
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
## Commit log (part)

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2024-12-09 First draft of automated lab
